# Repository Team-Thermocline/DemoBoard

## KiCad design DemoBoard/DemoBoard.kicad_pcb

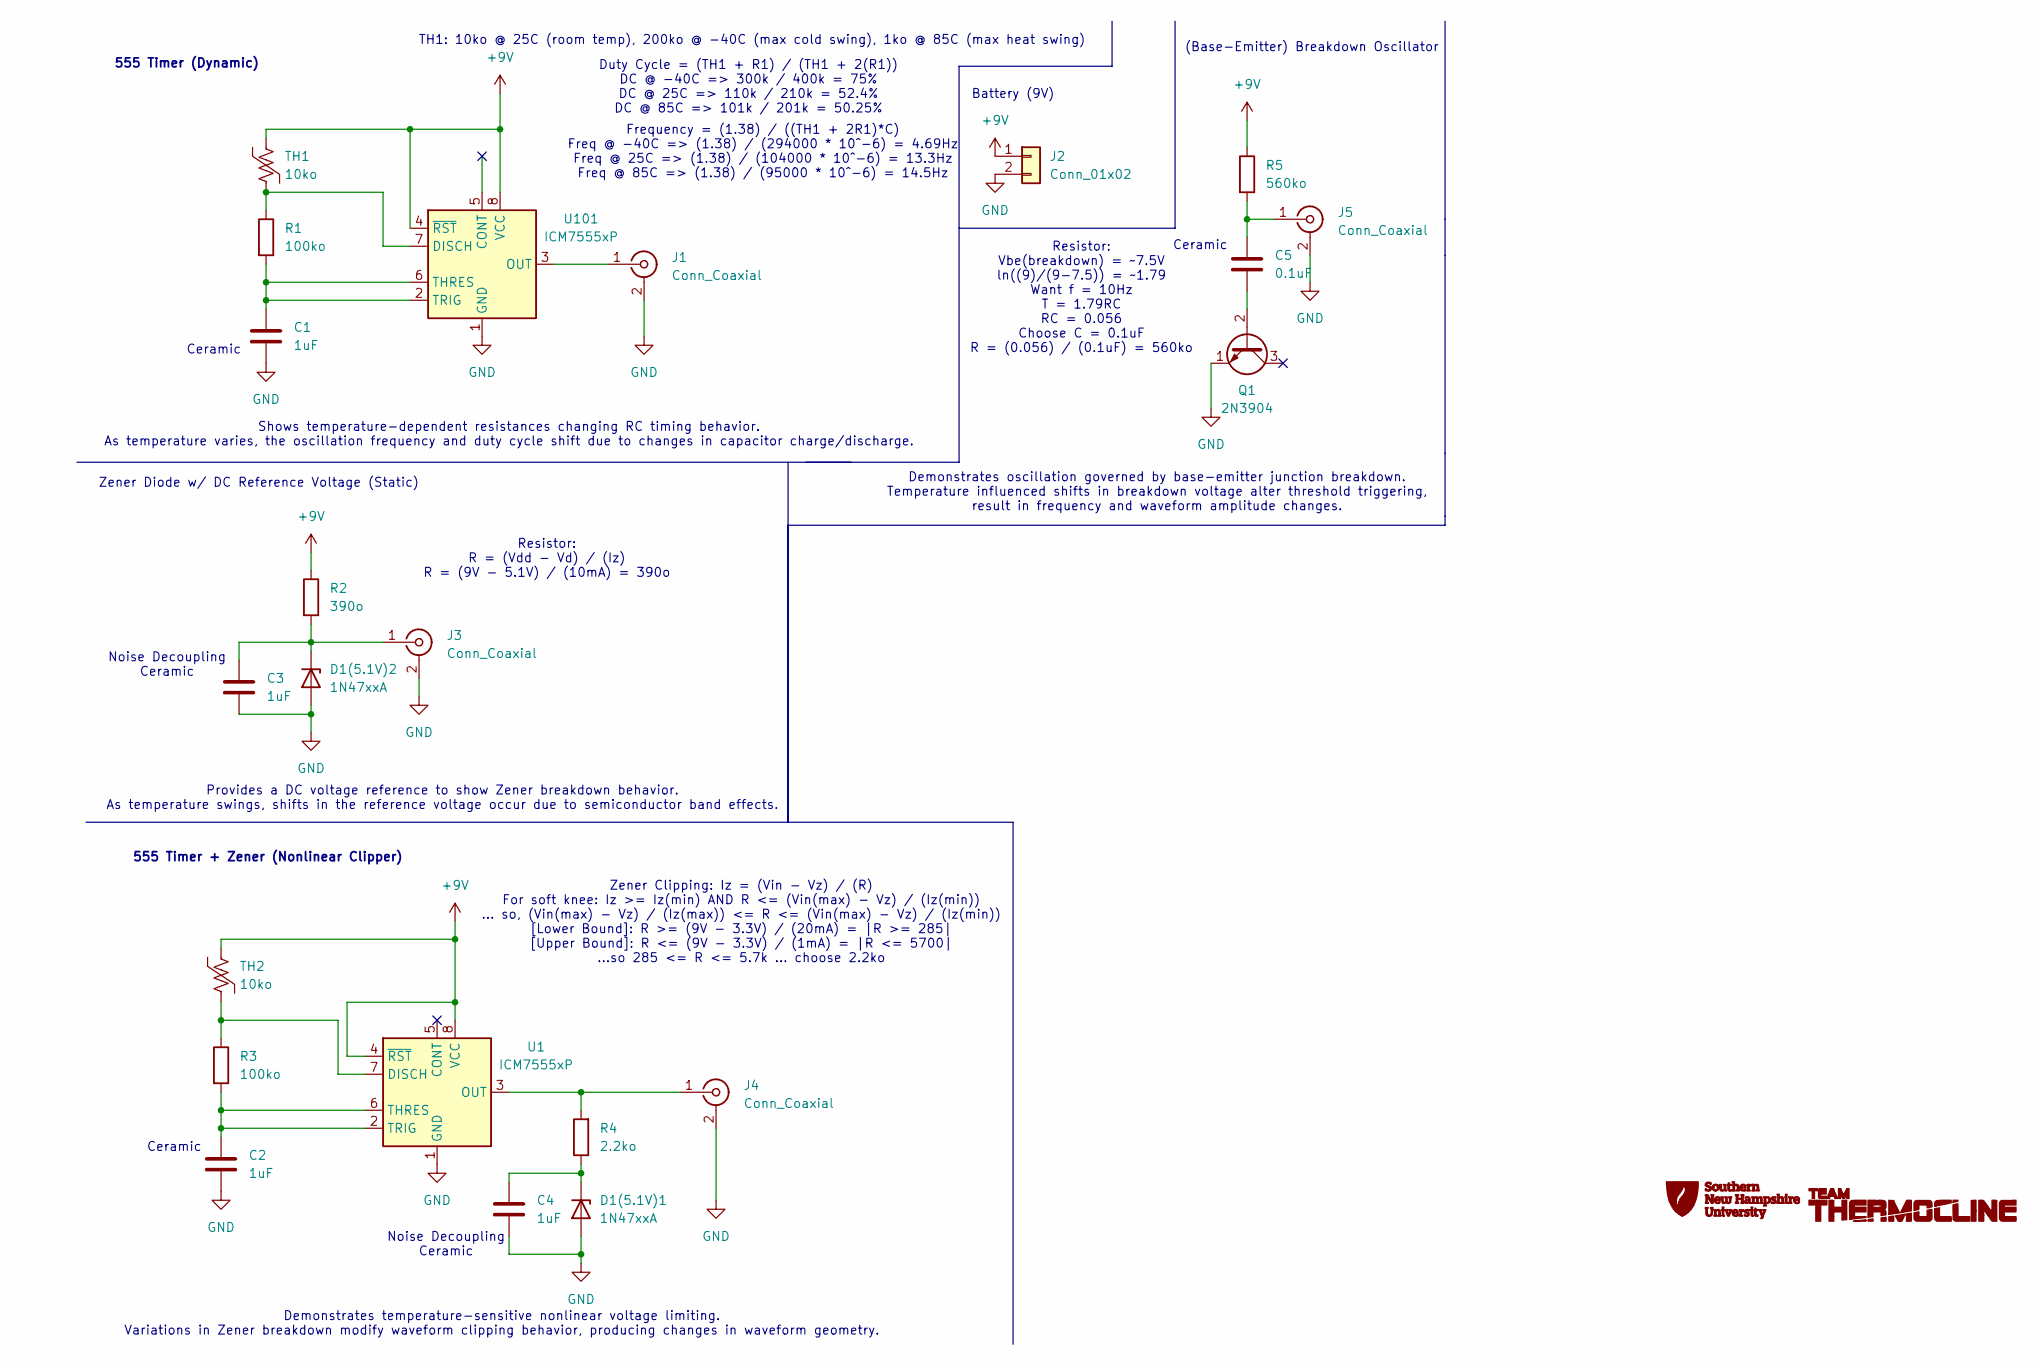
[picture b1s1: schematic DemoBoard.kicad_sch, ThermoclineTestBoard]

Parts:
C1, C2, C3, C4: 1uF; C_0805_2012Metric; LCSC# C28323
C5: 0.1uF; C_0805_2012Metric; LCSC# C49678
D1(5.1V)1, D1(5.1V)2: 1N47xxA; D_DO-41_SOD81_P10.16mm_Horizontal; LCSC# C7441074
J1, J3, J4, J5: Conn_Coaxial; HL-BNC-KHDA; LCSC# C19712152
J2: Conn_01x02; SolderWire-1.5sqmm_1x02_P6mm_D1.7mm_OD3mm_Relief
Q1: 2N3904; TO-92_Inline; LCSC# C50176433
R1, R3: 100ko; R_0805_2012Metric; LCSC# C149504
R2: 390o; R_0805_2012Metric; LCSC# C5555532
R4: 2.2ko; R_0805_2012Metric; LCSC# C17520
R5: 560ko; C_0805_2012Metric; LCSC# C2933556
TH1, TH2: 10ko; R_0805_2012Metric; LCSC# C141588
U1, U101: ICM7555xP; DIP-8_W7.62mm; LCSC# C7432184

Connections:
+9V: J2.1, R2.1, R5.1, TH1.2, TH2.2, U1.4 (~RST), U1.8 (VCC), U101.4 (~RST), U101.8 (VCC)
GND: C1.2, C2.2, C3.2, C4.2, D1(5.1V)1.2 (A), D1(5.1V)2.2 (A), J1.2 (Ext), J2.2, J3.2 (Ext), J4.2 (Ext), J5.2 (Ext), Q1.1 (E), U1.1 (GND), U101.1 (GND)
unnamed: C4.1, D1(5.1V)1.1 (K), R4.1
unnamed: C3.1, D1(5.1V)2.1 (K), J3.1 (In), R2.2
unnamed: J1.1 (In), U101.3 (OUT)
unnamed: J4.1 (In), R4.2, U1.3 (OUT)
unnamed: C5.1, J5.1 (In), R5.2
unnamed: C5.2, Q1.2 (B)
unnamed: R3.1, TH2.1, U1.7 (DISCH)
unnamed: C2.1, R3.2, U1.2 (TRIG), U1.6 (THRES)
unnamed: R1.1, TH1.1, U101.7 (DISCH)
unnamed: C1.1, R1.2, U101.2 (TRIG), U101.6 (THRES)

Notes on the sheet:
Ceramic
Noise Decoupling Ceramic
Zener Diode w/ DC Reference Voltage (Static)
Shows temperature-dependent resistances changing RC timing behavior. As temperature varies, the oscillation frequency and duty cycle shift due to changes in capacitor charge/discharge.
Resistor: Vbe(breakdown) = ~7.5V ln((9)/(9-7.5)) = ~1.79 Want f = 10Hz T = 1.79RC RC = 0.056 Choose C = 0.1uF R = (0.056) / (0.1uF) = 560ko
Zener Clipping: Iz = (Vin - Vz) / (R) For soft knee: Iz >= Iz(min) AND R <= (Vin(max) - Vz) / (Iz(min)) ... so, (Vin(max) - Vz) / (Iz(max)) <= R <= (Vin(max) - Vz) / (Iz(min)) [Lower Bound]: R >= (9V - 3.3V) / (20mA) = |R >= 285| [Upper Bound]: R <= (9V - 3.3V) / (1mA) = |R <= 5700| ...so 285 <= R 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
Duty Cycle = (TH1 + R1) / (TH1 + 2(R1)) DC @ -40C => 300k / 400k = 75% DC @ 25C => 110k / 210k = 52.4% DC @ 85C => 101k / 201k = 50.25%
Demonstrates temperature-sensitive nonlinear voltage limiting. Variations in Zener breakdown modify waveform clipping behavior, producing changes in waveform geometry.
Battery (9V)
Resistor: R = (Vdd - Vd) / (Iz) R = (9V - 5.1V) / (10mA) = 390o
555 Timer + Zener (Nonlinear Clipper)
Frequency = (1.38) / ((TH1 + 2R1)*C) Freq @ -40C => (1.38) / (294000 * 10^-6) = 4.69Hz Freq @ 25C => (1.38) / (104000 * 10^-6) = 13.3Hz Freq @ 85C => (1.38) / (95000 * 10^-6) = 14.5Hz
Demonstrates oscillation governed by base-emitter junction breakdown. Temperature influenced shifts in breakdown voltage alter threshold triggering, result in frequency and waveform amplitude changes.
555 Timer (Dynamic)
Provides a DC voltage reference to show Zener breakdown behavior. As temperature swings, shifts in the reference voltage occur due to semiconductor band effects.
TH1: 10ko @ 25C (room temp), 200ko @ -40C (max cold swing), 1ko @ 85C (max heat swing)
(Base-Emitter) Breakdown Oscillator

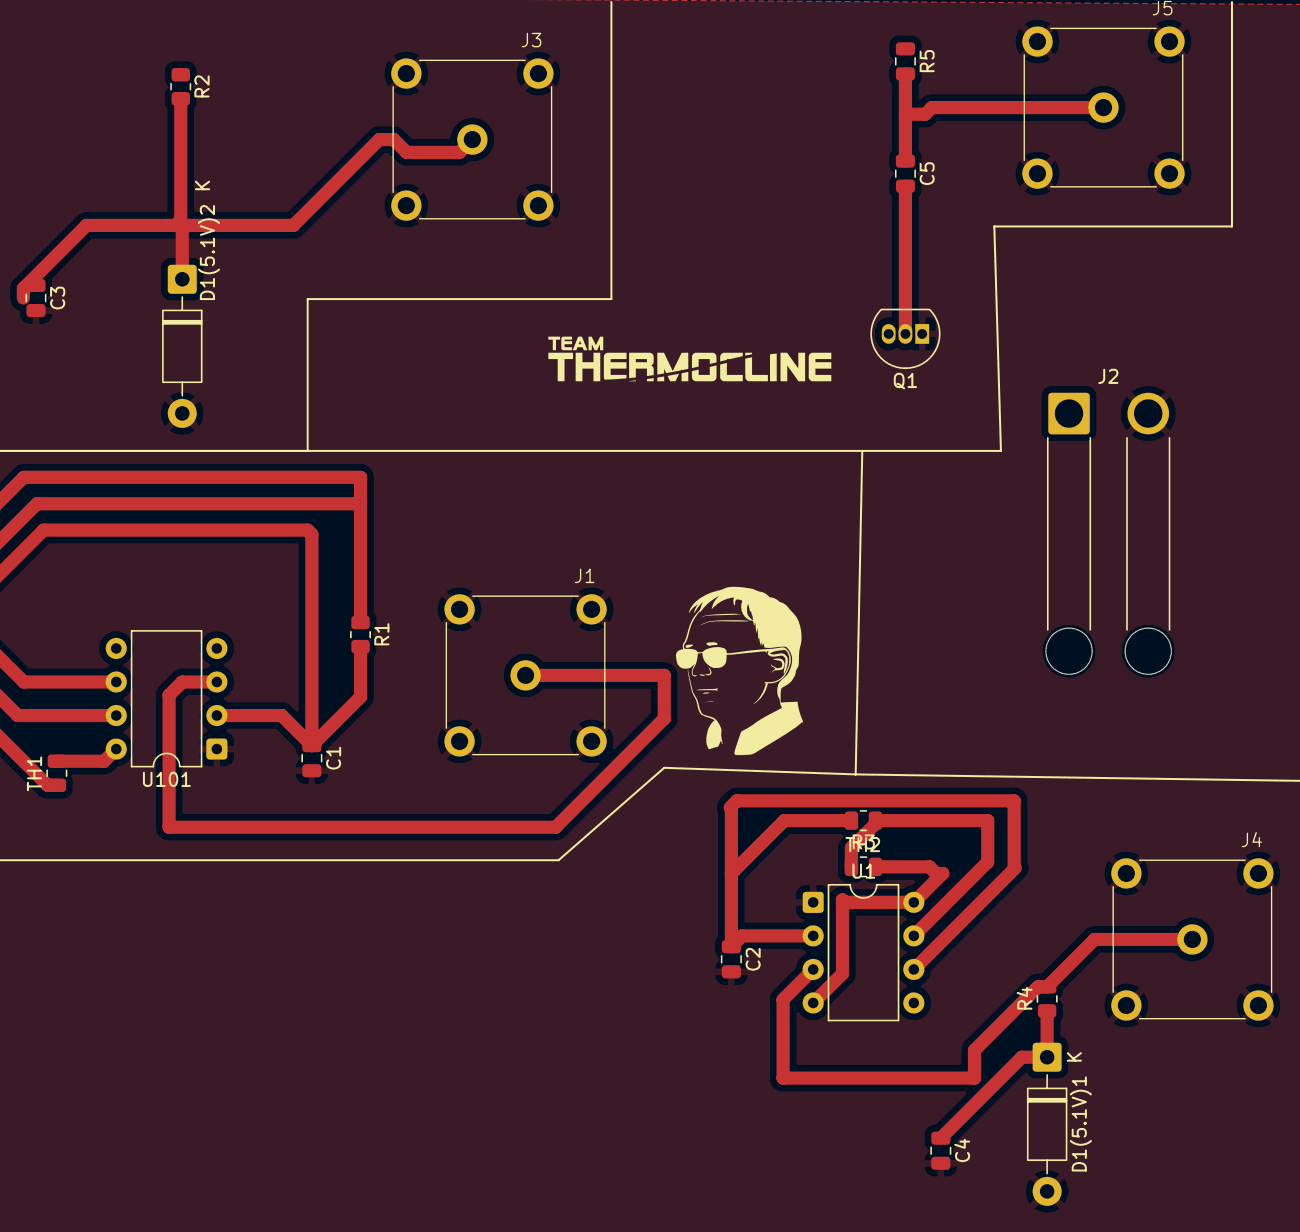
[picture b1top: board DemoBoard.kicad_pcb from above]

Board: 2 copper layers, 22 parts (0 on the bottom side), 12 nets.

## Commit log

2026-02-13 Clean repo
2026-02-18 Updated 555 Timer + Tunnel Diode (Circuit?)
    555 needs resistor ratio + tunnel diode (too expensive?) / what else could be used in its place?
2026-02-19 Added more blocks for demo testing
    Zener + DC Ref
    Zener + AC Ref (output of 555)
    Base-Emitter breakdown oscillator
2026-02-19 Added a comment
2026-02-20 Add KHDA BNC connector from upstream, include/pop P/N in sch sheet
2026-02-25 Inital layout
2026-03-17 Sectioned Everything on PCB
    Drew Traces and such
